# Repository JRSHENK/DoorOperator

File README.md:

This door operator uses an ESP32 to control 2 overhead door operator motors. The 2 Liftmaster 41D749 DC replacement motors are each driven by a BTS7960B H-bridge module (BT-2). The entire system is powered using (8) 18650 batteries I recovered from damage power tool battery packs that get trickle charged by a 16VDC supply. I monitor the battery voltage and motor currents using an INA219 module on each motor. The current is monitored while the door is moving and stops the motor if the current is more than expected. An optical beam is used to detect obstructions and stop the door. The position of the door is tracked using the optical shaft encoder built into the Liftmaster motors I used. The ESP32 has build in hardware counters, which eliminate the need to use interrupts in the code. I also use a hall effect sensor as a limit switch in the fully closed position as a reference for the position encoder. It just sets the counter to zero when the door is closed. This eliminates any counter errors from accumulating over time and gives a zero reference when initially installing.

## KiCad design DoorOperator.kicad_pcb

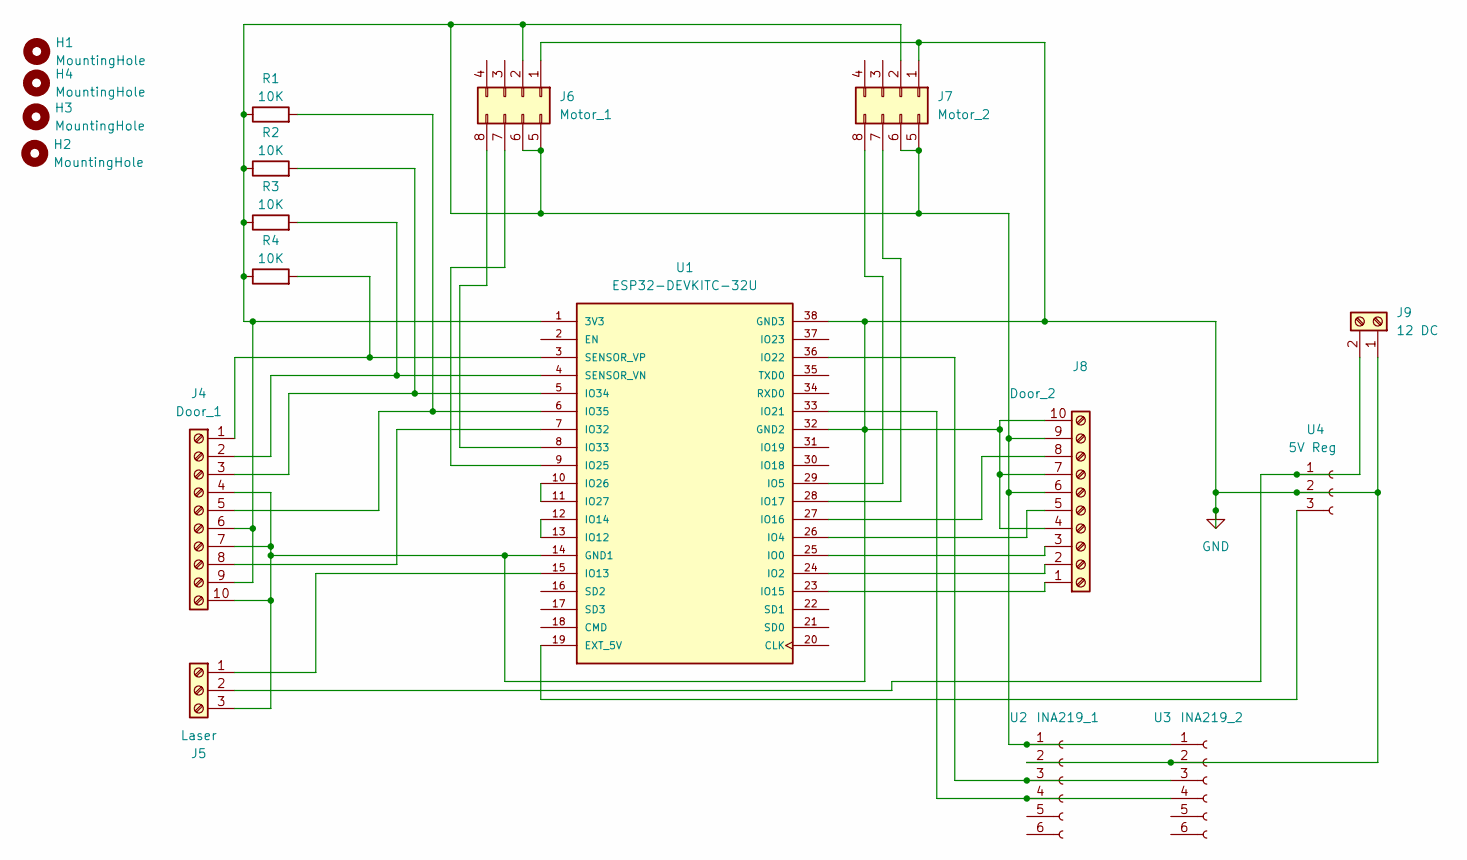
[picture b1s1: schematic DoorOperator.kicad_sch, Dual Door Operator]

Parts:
H1, H2, H3, H4: MountingHole; MountingHole_3.2mm_M3_Pad_TopBottom
J4: Door_1; TerminalBlock_Phoenix_MKDS-1,5-10_1x10_P5.00mm_Horizontal
J5: Laser; TerminalBlock_Phoenix_MKDS-1,5-3-5.08_1x03_P5.08mm_Horizont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
J6: Motor_1; PinHeader_2x04_P2.54mm_Vertical
J7: Motor_2; PinHeader_2x04_P2.54mm_Vertical
J8: Door_2; TerminalBlock_Phoenix_MKDS-1,5-10_1x10_P5.00mm_Horizontal
J9: 12 DC; TerminalBlock_Phoenix_MKDS-1,5-2_1x02_P5.00mm_Horizontal
R1, R2, R3, R4: 10K; R_Axial_DIN0207_L6.3mm_D2.5mm_P7.62mm_Horizontal
U1: ESP32-DEVKITC-32U; MODULE_ESP32-DEVKITC-32U; PARTREV N/A
U2: INA219_1; INA219_Module
U3: INA219_2; INA219_Module
U4: 5V Reg; PinSocket_1x03_P2.54mm_Vertical

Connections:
GND: J4.4, J4.7, J4.10, J5.3, J6.1, J7.1, J8.4, J8.7, J8.10, J9.1, U1.14 (GND1), U1.32 (GND2), U1.38 (GND3), U2.2, U3.2, U4.2
unnamed: J4.1, R4.2, U1.3 (SENSOR_VP)
unnamed: J4.2, R3.2, U1.4 (SENSOR_VN)
unnamed: J4.3, R2.2, U1.5 (IO34)
unnamed: J4.5, R1.2, U1.6 (IO35)
unnamed: J4.6, J4.9, J6.2, J6.5, J6.6, J7.2, J7.5, J7.6, J8.6, J8.9, R1.1, R2.1, R3.1, R4.1, U1.1 (3V3), U2.1, U3.1
unnamed: J4.8, U1.7 (IO32)
unnamed: J5.1, U1.15 (IO13)
unnamed: J5.2, J9.2, U4.1
unnamed: J6.7, U1.9 (IO25)
unnamed: J6.8, U1.8 (IO33)
unnamed: J7.7, U1.28 (IO17)
unnamed: J7.8, U1.29 (IO5)
unnamed: J8.1, U1.23 (IO15)
unnamed: J8.2, U1.24 (IO2)
unnamed: J8.3, U1.25 (IO0)
unnamed: J8.5, U1.26 (IO4)
unnamed: J8.8, U1.27 (IO16)
unnamed: U1.10 (IO26), U1.11 (IO27)
unnamed: U1.12 (IO14), U1.13 (IO12)
unnamed: U1.19 (EXT_5V), U4.3
unnamed: U1.33 (IO21), U2.4, U3.4
unnamed: U1.36 (IO22), U2.3, U3.3

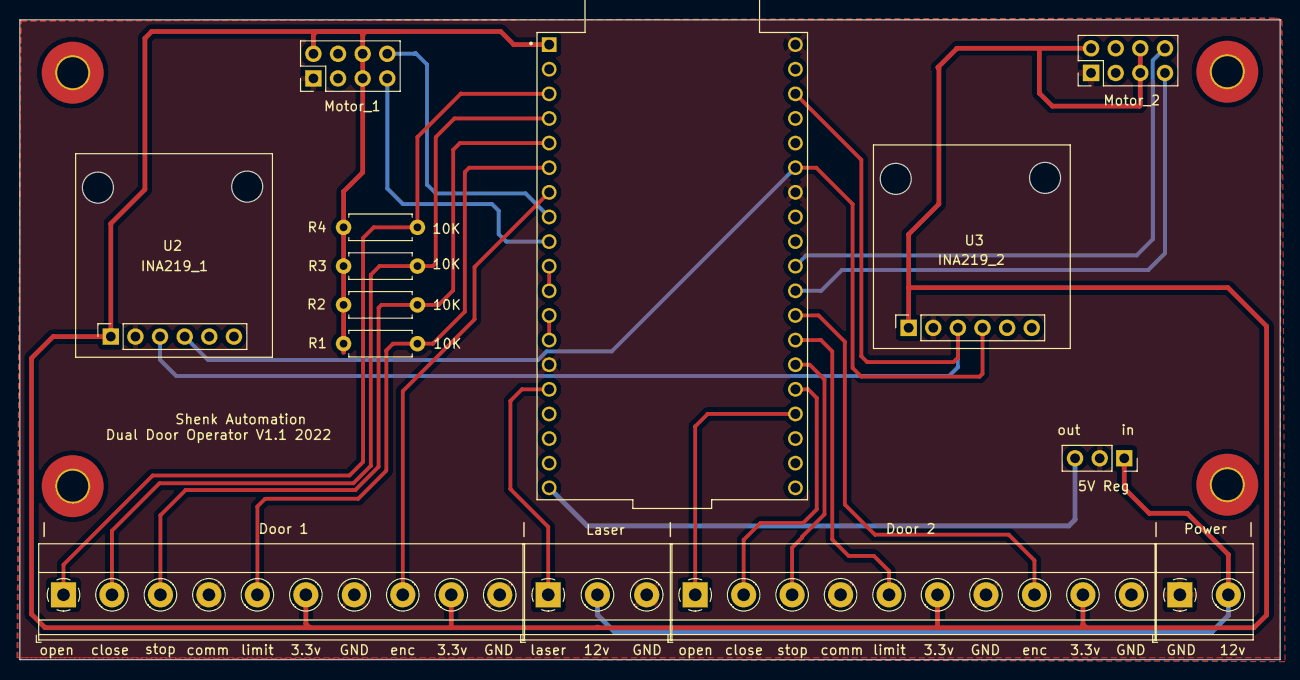
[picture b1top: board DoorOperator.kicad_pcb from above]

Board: 2 copper layers, 130.0 x 66.0 mm, 18 parts (0 on the bottom side), 23 nets.
